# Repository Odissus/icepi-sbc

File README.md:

# Icepi SBC

A low-cost single-board computer for the H3 CPU: A cheap yet powerful Linux device that you can take anywhere.

| Interested? [Subscribe to updates!](https://cyao.dev/subscribe.html) | Check out [Icepi Zero](https://github.com/cheyao/icepi-zero) too |
| -------------------------------------------------------------------- | ---------------------------------------------------------------- |

If there's a lot of people interested, there's a chance that I'll try to sell this at a relatively low price :P

## Features

- H3 Quad-Core ARM Cortex-A7 @ 1.296GHz CPU
    - Mali400 MP2 OpenGL ES 2.0 GPU
- 512MiB of DDR3 RAM, stable at 696MHz (Upgradable to 1GiB)
- Ethernet PHY, WiFi & Bluetooth
- GPDI video out
- USB connectors:
    - 2x USB-A 
    - 2x USB-C (One OTG port)
    - 1x USB-C 100W PD power port
- 3.5mm audio jack
- uSD card slot
- eMMC 5.1 storage

## System support

The single-board computer is capable of running Linux (debian) and Android ([H3Droid](https://h3droid.com/project)). It can output 4k video via it's GPDI-A connector, output a tty consol via UART, or act as an remote host via ssh.

It's small, compact form factor allows it to be a nice portable computer that you can take anywhere! It supports GPU acceleration and 4k video decoding, letting you view anything in full confort.

## PCB

[Check out the online version here](https://github.com/cheyao/icepi-sbc/tree/main/hardware).

The PCB is only 4 layered, ensuring minimal cost and overhead during production. But for mass production 6 layers is recommended, putting solid ground on In.1 and In.4, then copy the power plane to In.2 and In.3. (Impedance matching might be required depending on stackup)

The current setup uses [JLCPCB's](https://jlcpcb.com/) JLC04161H-3313 stackup, and the BOM is optimized for use there. Using other fabs would require re-tuning the DDR3, USB and GPDI traces.

## Open source

This project is licensed under the [Solderpad](/LICENSE) hardware license, granting the maximum amount of liberty :)

It is also OSHWA certified under the identifier [FR000029](https://certification.oshwa.org/fr000029.html).

## Contact

Any questions? Dm `@Cyao.` on Discord (Send a friend request or join the KiCAD Discord server) or send an email to `cyao _at_ duck.com`!

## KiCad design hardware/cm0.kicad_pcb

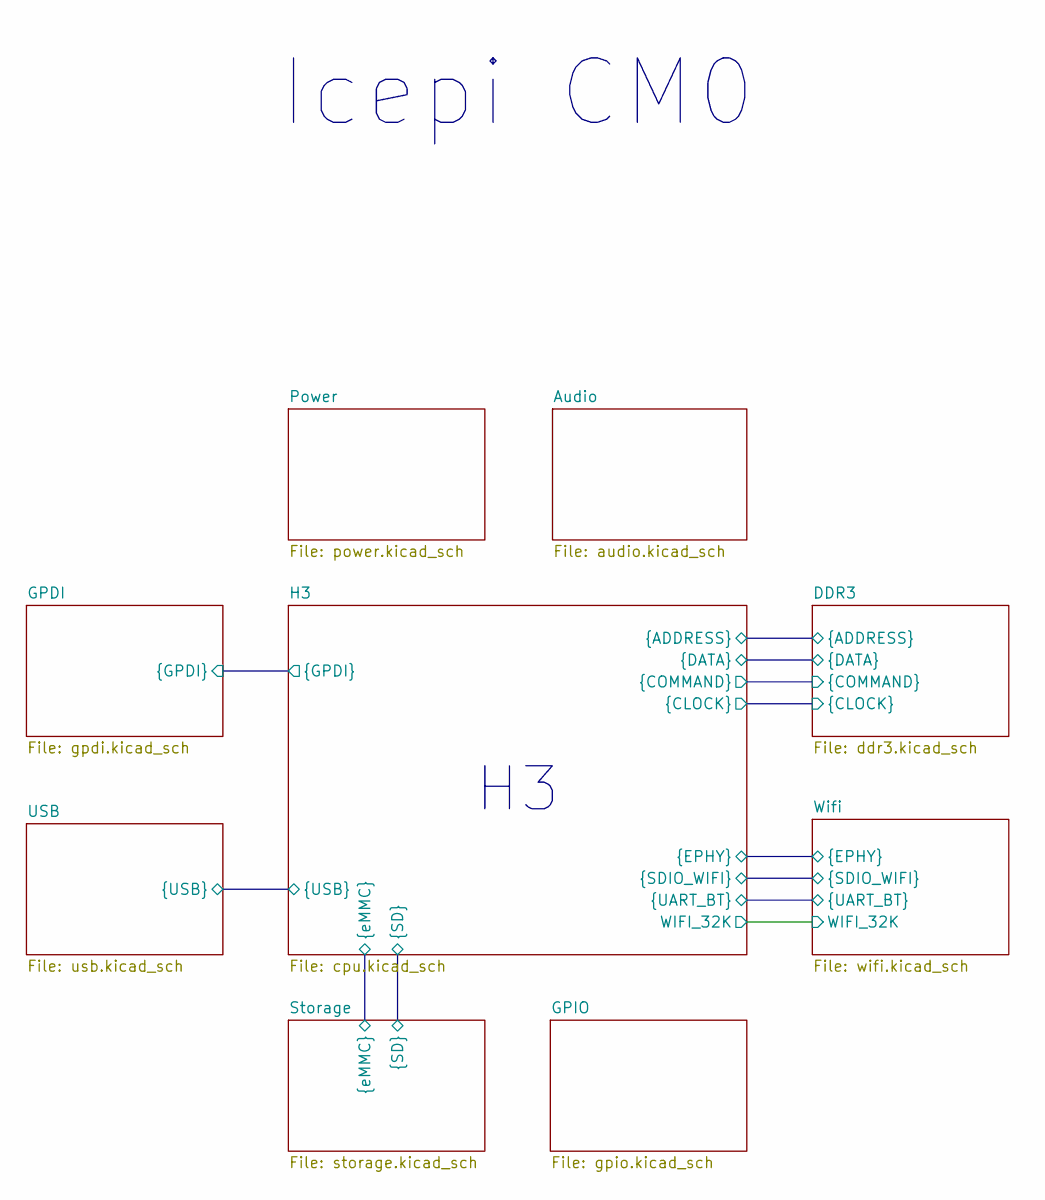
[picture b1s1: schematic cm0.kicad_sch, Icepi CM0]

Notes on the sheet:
Icepi CM0

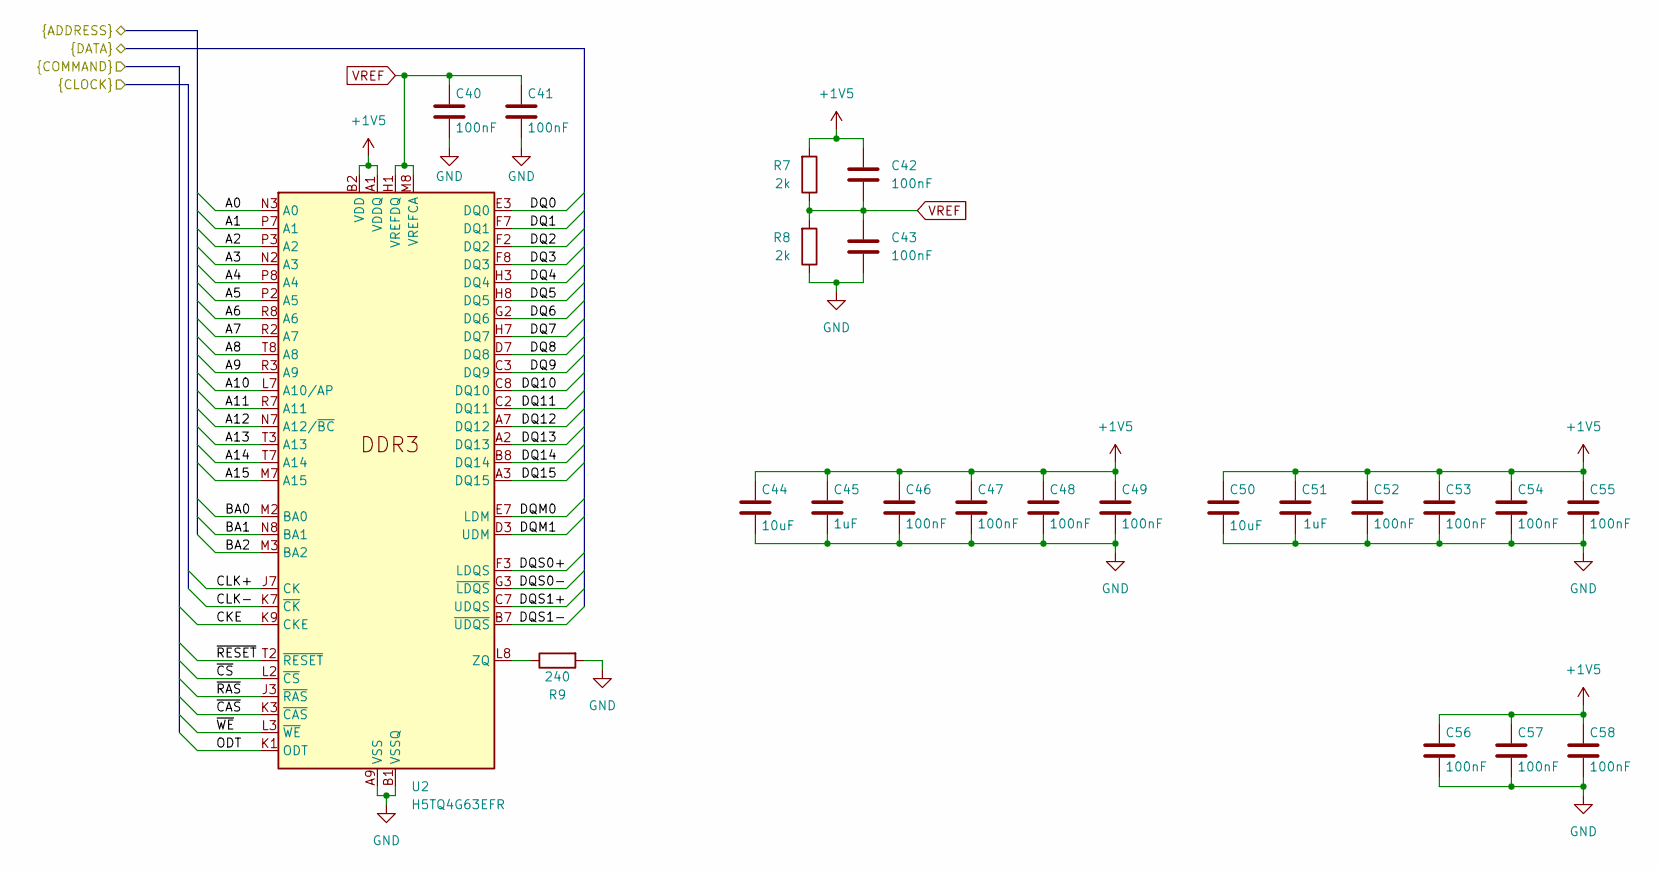
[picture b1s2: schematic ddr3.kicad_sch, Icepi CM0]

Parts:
C40, C41, C42, C43, C46, C47, C48, C49, C52, C53, C54, C55, C56, C57, C58: 100nF; C_0402_1005Metric; LCSC Part # C1525
C44, C50: 10uF; C_0603_1608Metric; LCSC Part # C19702
C45, C51: 1uF; C_0402_1005Metric; LCSC Part # C52923
R7, R8: 2k; R_0402_1005Metric; LCSC Part # C4109
R9: 240; R_0603_1608Metric; LCSC Part # C23350
U2: H5TQ4G63EFR; FBGA-96_7.5x13mm_Layout9x16_P0.8mm; LCSC Part # C2803259

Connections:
+1V5: C42.1, C44.1, C45.2, C46.1, C47.1, C48.1, C49.1, C50.1, C51.2, C52.1, C53.1, C54.1, C55.1, C56.1, C57.1, C58.1, R7.2, U2.A1 (VDDQ), U2.A8 (VDDQ), U2.B2 (VDD), U2.C1 (VDDQ), U2.C9 (VDDQ), U2.D2 (VDDQ), U2.D9 (VDD), U2.E9 (VDDQ), U2.F1 (VDDQ), U2.G7 (VDD), U2.H2 (VDDQ), U2.H9 (VDDQ), U2.K2 (VDD), U2.K8 (VDD), U2.N1 (VDD), U2.N9 (VDD), U2.R1 (VDD), U2.R9 (VDD); also elsewhere on the board
/DDR3/A0: U2.N3 (A0); also elsewhere on the board
/DDR3/A1: U2.P7 (A1); also elsewhere on the board
/DDR3/A2: U2.P3 (A2); also elsewhere on the board
/DDR3/A3: U2.N2 (A3); also elsewhere on the board
/DDR3/A4: U2.P8 (A4); also elsewhere on the board
/DDR3/A5: U2.P2 (A5); also elsewhere on the board
/DDR3/A6: U2.R8 (A6); also elsewhere on the board
/DDR3/A7: U2.R2 (A7); also elsewhere on the board
/DDR3/A8: U2.T8 (A8); also elsewhere on the board
/DDR3/A9: U2.R3 (A9); also elsewhere on the board
/DDR3/A10: U2.L7 (A10/AP); also elsewhere on the board
/DDR3/A11: U2.R7 (A11); also elsewhere on the board
/DDR3/A12: U2.N7 (A12/~BC); also elsewhere on the board
/DDR3/A13: U2.T3 (A13); also elsewhere on the board
/DDR3/A14: U2.T7 (A14); also elsewhere on the board
/DDR3/A15: U2.M7 (A15); also elsewhere on the board
/DDR3/BA0: U2.M2 (BA0); also elsewhere on the board
/DDR3/BA1: U2.N8 (BA1); also elsewhere on the board
/DDR3/BA2: U2.M3 (BA2); also elsewhere on the board
/DDR3/CKE: U2.K9 (CKE); also elsewhere on the board
/DDR3/CLK+: U2.J7 (CK); also elsewhere on the board
/DDR3/CLK-: U2.K7 (~CK); also elsewhere on the board
/DDR3/DQ0: U2.E3 (DQ0); also elsewhere on the board
/DDR3/DQ1: U2.F7 (DQ1); also elsewhere on the board
/DDR3/DQ2: U2.F2 (DQ2); also elsewhere on the board
/DDR3/DQ3: U2.F8 (DQ3); also elsewhere on the board
/DDR3/DQ4: U2.H3 (DQ4); also elsewhere on the board
/DDR3/DQ5: U2.H8 (DQ5); also elsewhere on the board
/DDR3/DQ6: U2.G2 (DQ6); also elsewhere on the board
/DDR3/DQ7: U2.H7 (DQ7); also elsewhere on the board
/DDR3/DQ8: U2.D7 (DQ8); also elsewhere on the board
/DDR3/DQ9: U2.C3 (DQ9); also elsewhere on the board
/DDR3/DQ10: U2.C8 (DQ10); also elsewhere on the board
/DDR3/DQ11: U2.C2 (DQ11); also elsewhere on the board
/DDR3/DQ12: U2.A7 (DQ12); also elsewhere on the board
/DDR3/DQ13: U2.A2 (DQ13); also elsewhere on the board
/DDR3/DQ14: U2.B8 (DQ14); also elsewhere on the board
/DDR3/DQ15: U2.A3 (DQ15); also elsewhere on the board
/DDR3/DQM0: U2.E7 (LDM); also elsewhere on the board
/DDR3/DQM1: U2.D3 (UDM); also elsewhere on the board
/DDR3/DQS0+: U2.F3 (LDQS); also elsewhere on the board
/DDR3/DQS0-: U2.G3 (~LDQS); also elsewhere on the board
/DDR3/DQS1+: U2.C7 (UDQS); also elsewhere on the board
/DDR3/DQS1-: U2.B7 (~UDQS); also elsewhere on the board
/DDR3/ODT: U2.K1 (ODT); also elsewhere on the board
/DDR3/~CAS: U2.K3 (~CAS); also elsewhere on the board
/DDR3/~CS: U2.L2 (~CS); also elsewhere on the board
/DDR3/~RAS: U2.J3 (~RAS); also elsewhere on the board
/DDR3/~RESET: U2.T2 (~RESET); also elsewhere on the board
/DDR3/~WE: U2.L3 (~WE); also elsewhere on the board
GND: C40.2, C41.2, C43.2, C44.2, C45.1, C46.2, C47.2, C48.2, C49.2, C50.2, C51.1, C52.2, C53.2, C54.2, C55.2, C56.2, C57.2, C58.2, R8.1, R9.2, U2.A9 (VSS), U2.B1 (VSSQ), U2.B3 (VSS), U2.B9 (VSSQ), U2.D1 (VSSQ), U2.D8 (VSSQ), U2.E1 (VSS), U2.E2 (VSSQ), U2.E8 (VSSQ), U2.F9 (VSSQ), U2.G1 (VSSQ), U2.G8 (VSS), U2.G9 (VSSQ), U2.J2 (VSS), U2.J8 (VSS), U2.M1 (VSS), U2.M9 (VSS), U2.P1 (VSS), U2.P9 (VSS), U2.T1 (VSS), U2.T9 (VSS); also elsewhere on the board
unnamed: R9.1, U2.L8 (ZQ)
VREF: C40.1, C41.1, C42.2, C43.1, R7.1, R8.2, U2.H1 (VREFDQ), U2.M8 (VREFCA); also elsewhere on the board

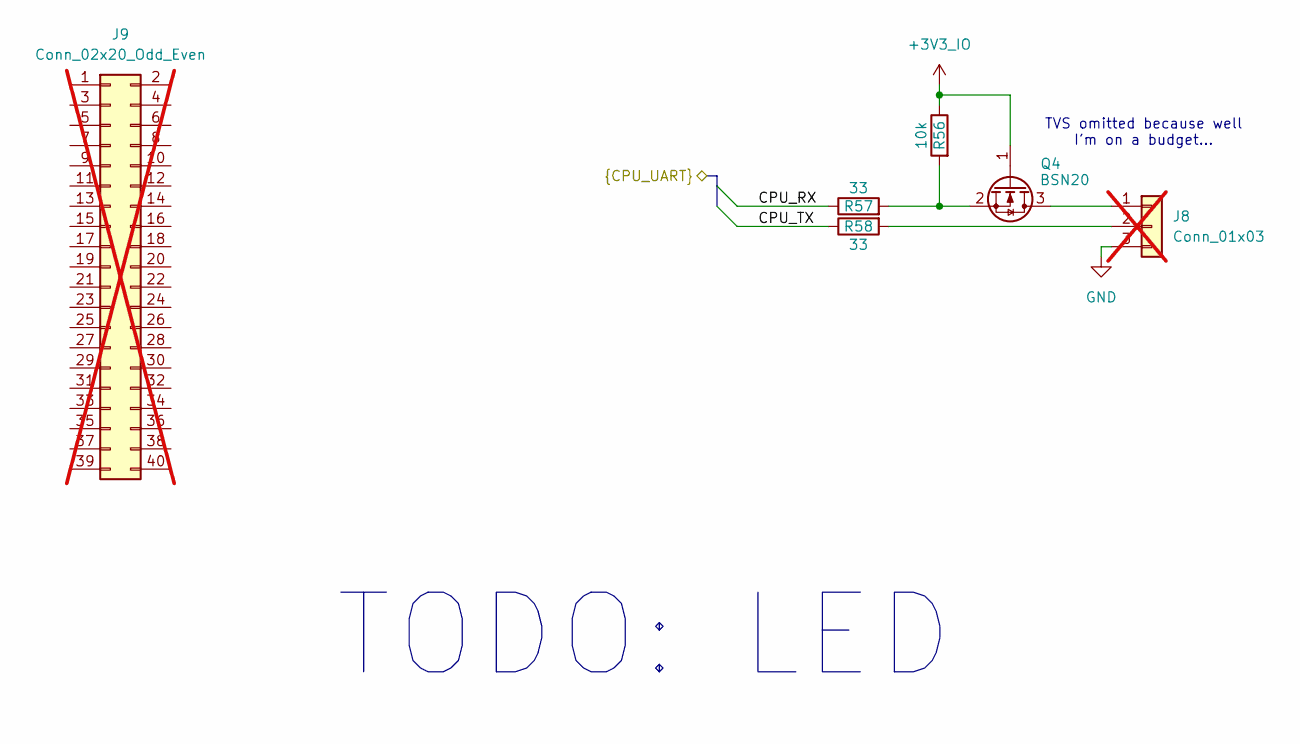
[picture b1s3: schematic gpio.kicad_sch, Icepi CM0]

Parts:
J8: Conn_01x03; PinHeader_1x03_P2.54mm_Vertical; not fitted
J9: Conn_02x20_Odd_Even; PinHeader_2x20_P2.54mm_Vertical; not fitted
Q4: BSN20; SOT-23; LCSC Part # C116157
R56: 10k; R_0402_1005Metric; LCSC Part # C25744
R57, R58: 33; R_0402_1005Metric; LCSC Part # C25105

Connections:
+3V3_IO: Q4.1 (G), R56.1; also elsewhere on the board
/GPIO/CPU_RX: R57.1; also elsewhere on the board
/GPIO/CPU_TX: R58.1; also elsewhere on the board
GND: J8.3; also elsewhere on the board
unnamed: J8.1, Q4.3 (D)
unnamed: J8.2, R58.2
unnamed: Q4.2 (S), R56.2, R57.2

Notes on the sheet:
TODO: LED
TVS omitted because well I'm on a budget...

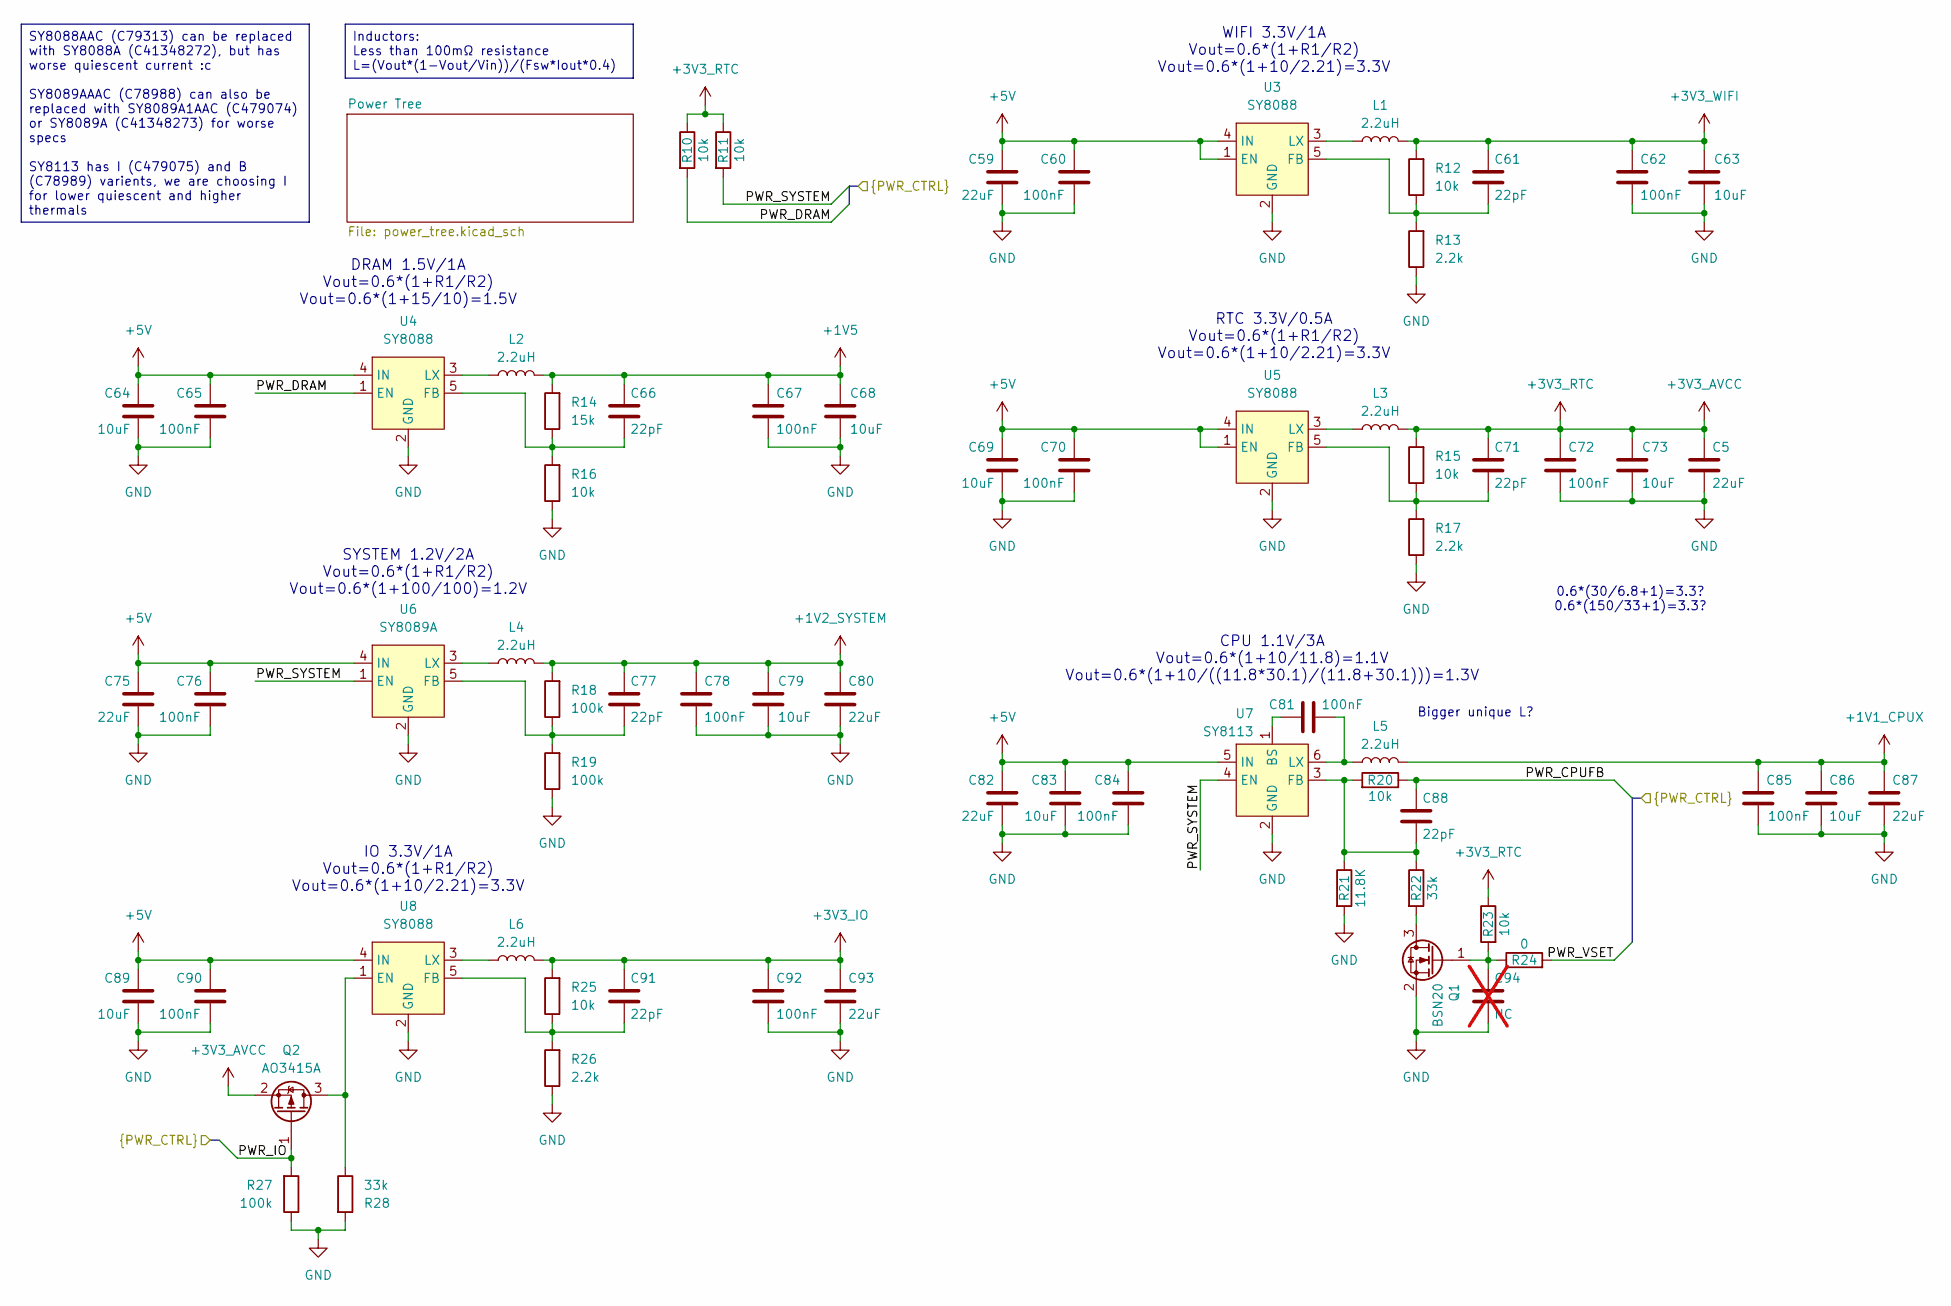
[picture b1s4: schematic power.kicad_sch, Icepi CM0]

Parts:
C5, C59, C75, C80, C82, C87, C93: 22uF; C_0603_1608Metric; LCSC Part # C59461
C60, C62, C65, C67, C70, C72, C76, C78, C81, C84, C85, C90, C92: 100nF; C_0402_1005Metric; LCSC Part # C1525
C61, C66, C71, C77, C88, C91: 22pF; C_0402_1005Metric; LCSC Part # C1555
C63, C64, C68, C69, C73, C79, C83, C86, C89: 10uF; C_0603_1608Metric; LCSC Part # C19702
C94: NC; C_0402_1005Metric; not fitted
L1, L2, L3, L6: 2.2uH; L_Sunlord_SWPA3015S; LCSC Part # C19734
L4, L5: 2.2uH; L_Sunlord_SWPA4030S; LCSC Part # C135262
Q1: BSN20; SOT-23; LCSC Part # C116157
Q2: AO3415A; SOT-23; LCSC Part # C347479
R10, R11, R12, R15, R16, R20, R23, R25: 10k; R_0402_1005Metric; LCSC Part # C25744
R13, R17, R26: 2.2k; R_0402_1005Metric; LCSC Part # C25879
R14: 15k; R_0402_1005Metric; LCSC Part # C25756
R18, R19, R27: 100k; R_0402_1005Metric; LCSC Part # C25741
R21: 11.8K; R_0402_1005Metric; LCSC Part # C2929934
R22, R28: 33k; R_0402_1005Metric; LCSC Part # C25779
R24: 0; R_0402_1005Metric; LCSC Part # C17168
U3, U4, U5, U8: SY8088; SOT-23-5; LCSC Part # C79313
U6: SY8089A; SOT-23-5; LCSC Part # C78988
U7: SY8113; TSOT-23-6; LCSC Part # C479075

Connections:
+1V1_CPUX: C85.2, C86.1, C87.1, L5.2; also elsewhere on the board
+1V2_SYSTEM: C77.1, C78.2, C79.1, C80.1, L4.2, R18.2; also elsewhere on the board
+1V5: C66.1, C67.2, C68.1, L2.2, R14.2; also elsewhere on the board
+3V3_AVCC: C5.1, C71.1, C72.2, C73.1, L3.2, Q2.2 (S), R10.1, R11.1, R15.2, R23.1; also elsewhere on the board
+3V3_IO: C91.1, C92.2, C93.1, L6.2, R25.2; also elsewhere on the board
+3V3_WIFI: C61.1, C62.2, C63.1, L1.2, R12.2; also elsewhere on the board
+5V: C59.1, C60.2, C64.1, C65.2, C69.1, C70.2, C75.1, C76.2, C82.1, C83.1, C84.2, C89.1, C90.2, U3.1 (EN), U3.4 (IN), U4.4 (IN), U5.1 (EN), U5.4 (IN), U6.4 (IN), U7.5 (IN), U8.4 (IN); also elsewhere on the board
/H3/PWR_CPUFB: C88.1, R20.1; also elsewhere on the board
/H3/PWR_DRAM: R10.2, U4.1 (EN); also elsewhere on the board
/H3/PWR_IO: Q2.1 (G), R27.2; also elsewhere on the board
/H3/PWR_SYSTEM: R11.2, U6.1 (EN), U7.4 (EN); also elsewhere on the board
/H3/PWR_VSET: R24.2; also elsewhere on the board
GND: C5.2, C59.2, C60.1, C62.1, C63.2, C64.2, C65.1, C67.1, C68.2, C69.2, C70.1, C72.1, C73.2, C75.2, C76.1, C78.1, C79.2, C80.2, C82.2, C83.2, C84.1, C85.1, C86.2, C87.2, C89.2, C90.1, C92.1, C93.2, C94.2, Q1.2 (S), R13.1, R16.1, R17.1, R19.1, R21.2, R26.1, R27.1, R28.2, U3.2 (GND), U4.2 (GND), U5.2 (GND), U6.2 (GND), U7.2 (GND), U8.2 (GND); also elsewhere on the board
unnamed: Q1.3 (D), R22.2
unnamed: C94.1, Q1.1 (G), R23.2, R24.1
unnamed: Q2.3 (D), R28.1, U8.1 (EN)
unnamed: C61.2, R12.1, R13.2, U3.5 (FB)
unnamed: L1.1, U3.3 (LX)
unnamed: C66.2, R14.1, R16.2, U4.5 (FB)
unnamed: L2.1, U4.3 (LX)
unnamed: C71.2, R15.1, R17.2, U5.5 (FB)
unnamed: L3.1, U5.3 (LX)
unnamed: C77.2, R18.1, R19.2, U6.5 (FB)
unnamed: L4.1, U6.3 (LX)
unnamed: C81.2, U7.1 (BS)
unnamed: C88.2, R20.2, R21.1, R22.1, U7.3 (FB)
unnamed: C81.1, L5.1, U7.6 (LX)
unnamed: C91.2, R25.1, R26.2, U8.5 (FB)
unnamed: L6.1, U8.3 (LX)

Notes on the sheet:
SYSTEM 1.2V/2A Vout=0.6*(1+R1/R2) Vout=0.6*(1+100/100)=1.2V
WIFI 3.3V/1A Vout=0.6*(1+R1/R2) Vout=0.6*(1+10/2.21)=3.3V
0.6*(30/6.8+1)=3.3? 0.6*(150/33+1)=3.3?
RTC 3.3V/0.5A Vout=0.6*(1+R1/R2) Vout=0.6*(1+10/2.21)=3.3V
IO 3.3V/1A Vout=0.6*(1+R1/R2) Vout=0.6*(1+10/2.21)=3.3V
CPU 1.1V/3A Vout=0.6*(1+10/11.8)=1.1V Vout=0.6*(1+10/((11.8*30.1)/(11.8+30.1)))=1.3V
DRAM 1.5V/1A Vout=0.6*(1+R1/R2) Vout=0.6*(1+15/10)=1.5V
Bigger unique L?
SY8088AAC (C79313) can be replaced with SY8088A (C41348272), but has worse quiescent current :c SY8089AAAC (C78988) can also be replaced with SY8089A1AAC (C479074) or SY8089A (C41348273) for worse specs SY8113 has I (C479075) and B (C78989) varients, we are choosing I for lower quiescent and higher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
Inductors: Less than 100mΩ resistance L=(Vout*(1-Vout/Vin))/(Fsw*Iout*0.4)

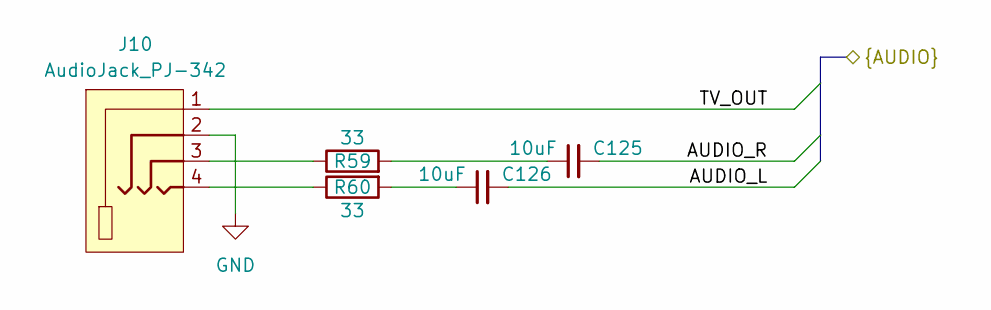
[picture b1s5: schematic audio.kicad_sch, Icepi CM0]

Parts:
C125, C126: 10uF; C_0603_1608Metric; LCSC Part # C19702
J10: AudioJack_PJ-342; Jack_3.5mm_SHOUHAN_PJ-342; LCSC Part # C7507452
R59, R60: 33; R_0402_1005Metric; LCSC Part # C25105

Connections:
/Audio/AUDIO_L: C126.2; also elsewhere on the board
/Audio/AUDIO_R: C125.2; also elsewhere on the board
/Audio/TV_OUT: J10.1; also elsewhere on the board
GND: J10.2; also elsewhere on the board
unnamed: C125.1, R59.2
unnamed: C126.1, R60.2
unnamed: J10.3, J10.5, R59.1
unnamed: J10.4, J10.6, R60.1

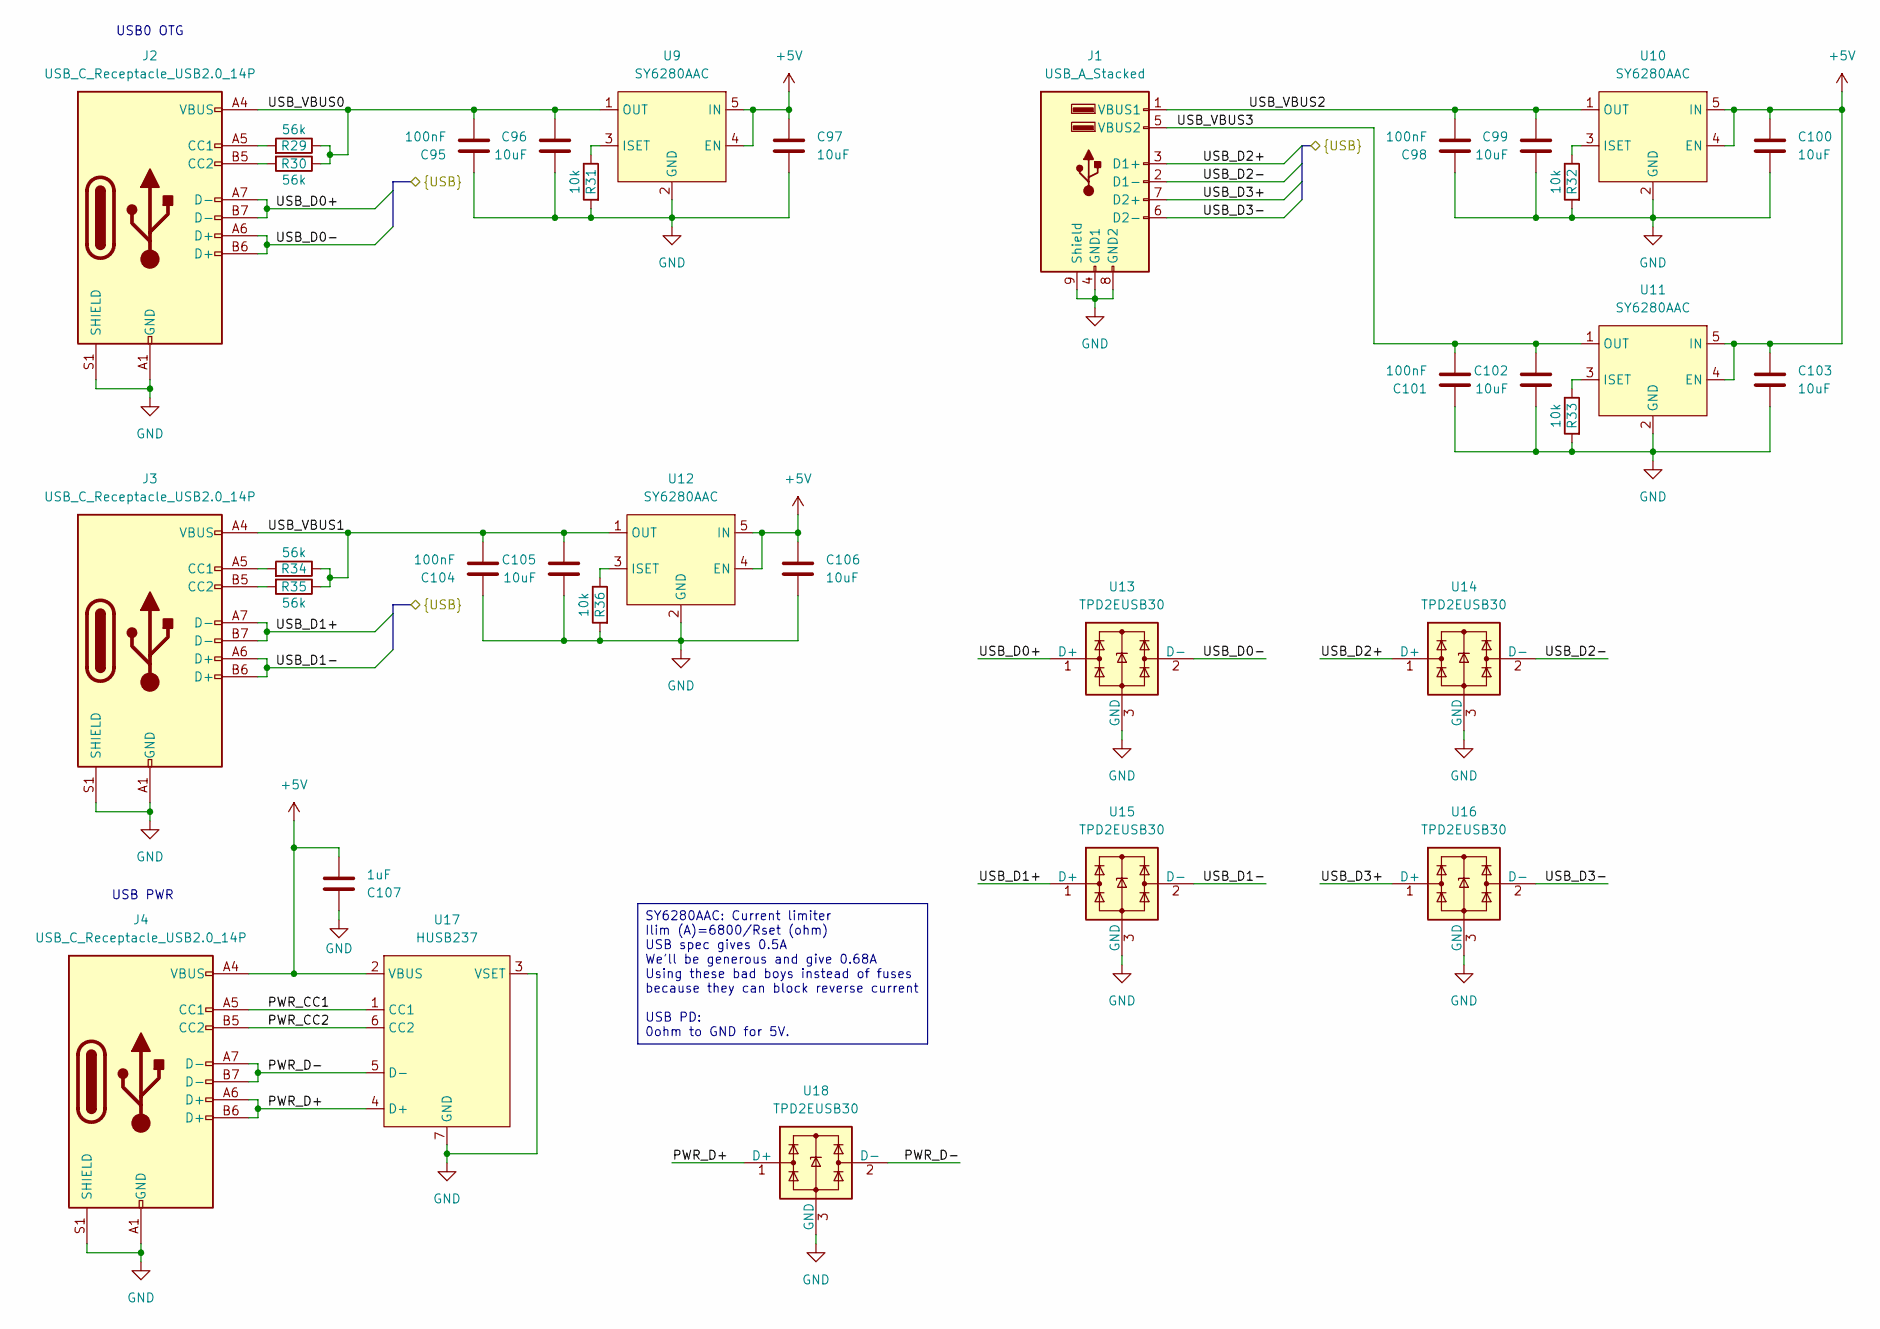
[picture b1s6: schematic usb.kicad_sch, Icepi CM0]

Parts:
C95, C98, C101, C104: 100nF; C_0402_1005Metric; LCSC Part # C1525
C96, C97, C99, C100, C102, C103, C105, C106: 10uF; C_0603_1608Metric; LCSC Part # C19702
C107: 1uF; C_0402_1005Metric; LCSC Part # C52923
J1: USB_A_Stacked; USB_A_SHOUHAN_AF_SS-JB17.6_Horizontal_Stacked; LCSC Part # C456021
J2, J3, J4: USB_C_Receptacle_USB2.0_14P; USB_C_Receptacle_HRO_TYPE-C-31-M-12; LCSC Part # C165948
R29, R30, R34, R35: 56k; R_0402_1005Metric; LCSC Part # C25796
R31, R32, R33, R36: 10k; R_0402_1005Metric; LCSC Part # C25744
U9, U10, U11, U12: SY6280AAC; SOT-23-5; LCSC Part # C55136
U13, U14, U15, U16, U18: TPD2EUSB30; Texas_DRT-3; LCSC Part # C5182099
U17: HUSB237; DFN-6-1EP_2x2mm_P0.65mm_EP1x1.6mm; LCSC Part # C22373734

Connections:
+5V: C97.1, C100.1, C103.1, C106.1, C107.2, J4.A4 (VBUS), J4.A9 (VBUS), J4.B4 (VBUS), J4.B9 (VBUS), U9.4 (EN), U9.5 (IN), U10.4 (EN), U10.5 (IN), U11.4 (EN), U11.5 (IN), U12.4 (EN), U12.5 (IN), U17.2 (VBUS); also elsewhere on the board
/H3/USB_D0+: J2.A7 (D-), J2.B7 (D-), U13.1 (D+); also elsewhere on the board
/H3/USB_D0-: J2.A6 (D+), J2.B6 (D+), U13.2 (D-); also elsewhere on the board
/H3/USB_D1+: J3.A7 (D-), J3.B7 (D-), U15.1 (D+); also elsewhere on the board
/H3/USB_D1-: J3.A6 (D+), J3.B6 (D+), U15.2 (D-); also elsewhere on the board
/USB/PWR_CC1: J4.A5 (CC1), U17.1 (CC1)
/USB/PWR_CC2: J4.B5 (CC2), U17.6 (CC2)
/USB/PWR_D+: J4.A6 (D+), J4.B6 (D+), U17.4 (D+), U18.1 (D+)
/USB/PWR_D-: J4.A7 (D-), J4.B7 (D-), U17.5 (D-), U18.2 (D-)
/USB/USB_VBUS0: C95.2, C96.1, J2.A4 (VBUS), J2.A9 (VBUS), J2.B4 (VBUS), J2.B9 (VBUS), R29.1, R30.1, U9.1 (OUT)
/USB/USB_VBUS1: C104.2, C105.1, J3.A4 (VBUS), J3.A9 (VBUS), J3.B4 (VBUS), J3.B9 (VBUS), R34.1, R35.1, U12.1 (OUT)
/USB/USB_VBUS2: C98.2, C99.1, J1.1 (VBUS1), U10.1 (OUT)
/USB/USB_VBUS3: C101.2, C102.1, J1.5 (VBUS2), U11.1 (OUT)
GND: C95.1, C96.2, C97.2, C98.1, C99.2, C100.2, C101.1, C102.2, C103.2, C104.1, C105.2, C106.2, C107.1, J1.4 (GND1), J1.8 (GND2), J1.9 (Shield), J2.A1 (GND), J2.A12 (GND), J2.B1 (GND), J2.B12 (GND), J2.S1 (SHIELD), J3.A1 (GND), J3.A12 (GND), J3.B1 (GND), J3.B12 (GND), J3.S1 (SHIELD), J4.A1 (GND), J4.A12 (GND), J4.B1 (GND), J4.B12 (GND), J4.S1 (SHIELD), R31.2, R32.2, R33.2, R36.2, U9.2 (GND), U10.2 (GND), U11.2 (GND), U12.2 (GND), U13.3 (GND), U14.3 (GND), U15.3 (GND), U16.3 (GND), U17.3 (VSET), U17.7 (GND), U18.3 (GND); also elsewhere on the board
unnamed: J2.A5 (CC1), R29.2
unnamed: J2.B5 (CC2), R30.2
unnamed: J3.A5 (CC1), R34.2
unnamed: J3.B5 (CC2), R35.2
unnamed: R31.1, U9.3 (ISET)
unnamed: R32.1, U10.3 (ISET)
unnamed: R33.1, U11.3 (ISET)
unnamed: R36.1, U12.3 (ISET)

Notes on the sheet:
USB0 OTG
USB PWR
SY6280AAC: Current limiter Ilim (A)=6800/Rset (ohm) USB spec gives 0.5A We'll be generous and give 0.68A Using these bad boys instead of fuses because they can block reverse current USB PD: 0ohm to GND for 5V.

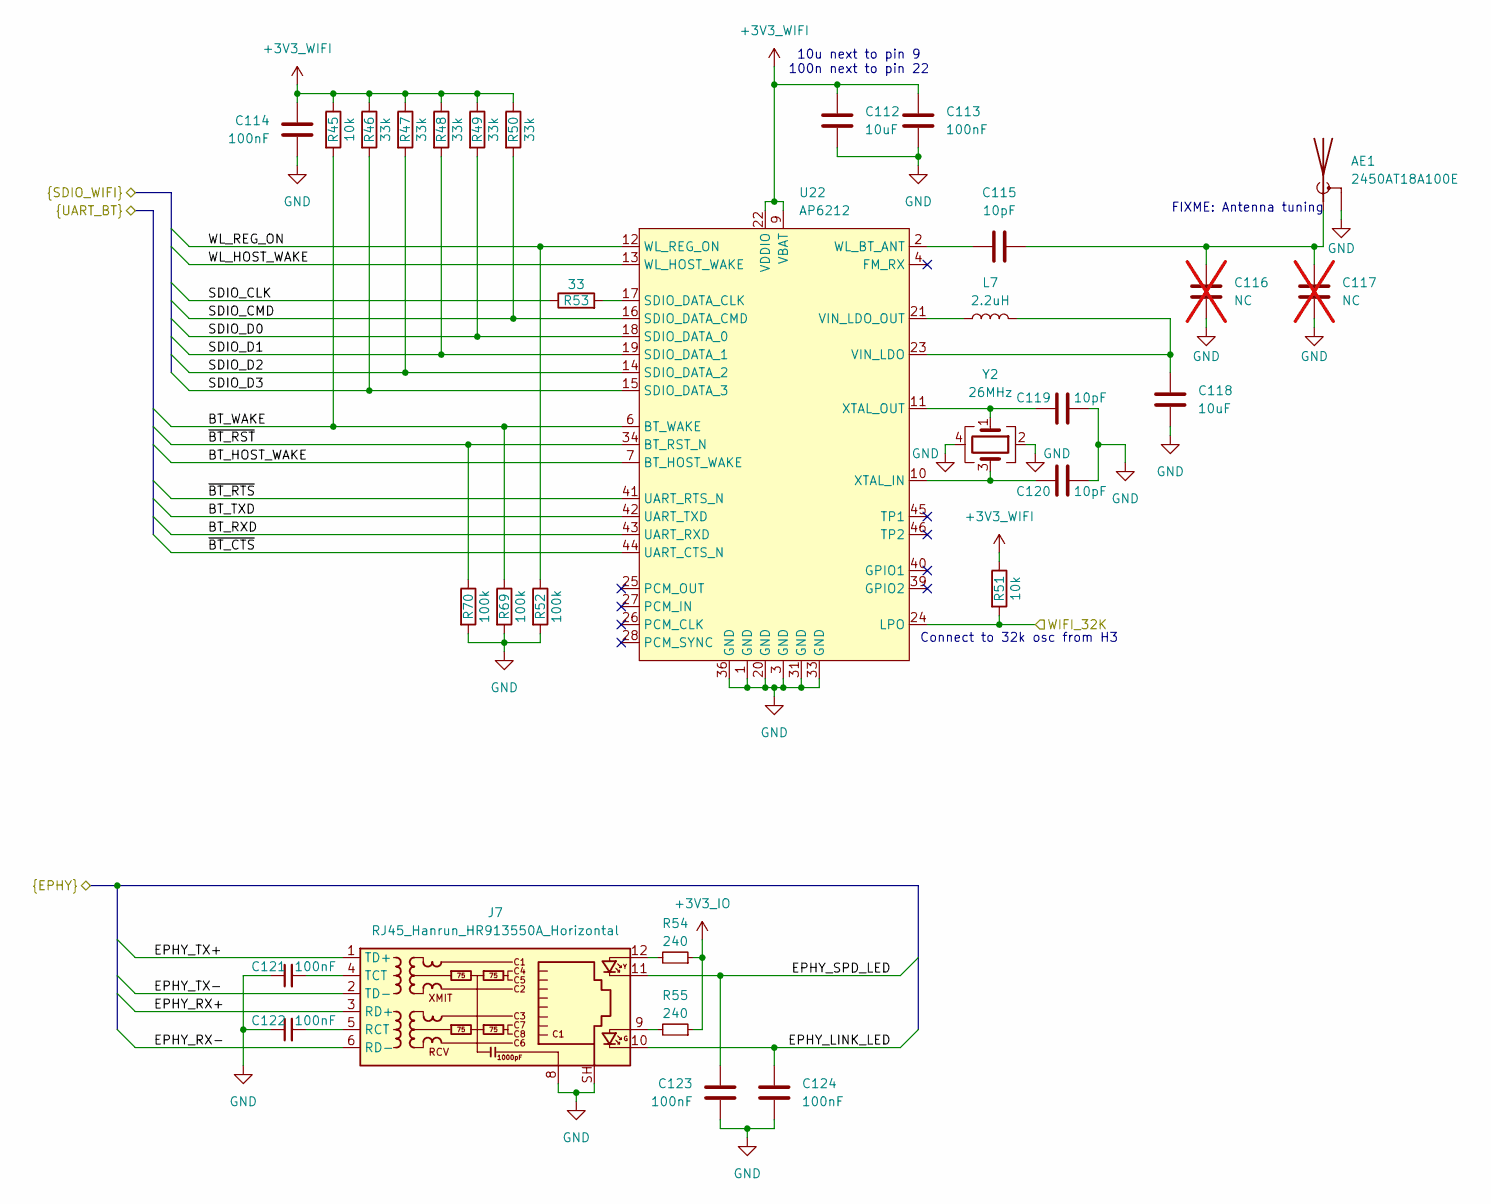
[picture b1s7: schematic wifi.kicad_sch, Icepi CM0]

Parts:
AE1: 2450AT18A100E; Johanson_2450AT18x100; LCSC Part # C89334
C112, C118: 10uF; C_0603_1608Metric; LCSC Part # C19702
C113, C114, C121, C122, C123, C124: 100nF; C_0402_1005Metric; LCSC Part # C1525
C115, C119, C120: 10pF; C_0402_1005Metric; LCSC Part # C32949
C116, C117: NC; C_0402_1005Metric; not fitted
J7: RJ45_Hanrun_HR913550A_Horizontal; RJ45_Hanrun_HR911105A_Horizontal; LCSC Part # C163507
L7: 2.2uH; L_Sunlord_SWPA3015S; LCSC Part # C19734
R45, R51: 10k; R_0402_1005Metric; LCSC Part # C25744
R46, R47, R48, R49, R50: 33k; R_0402_1005Metric; LCSC Part # C25779
R52, R69, R70: 100k; R_0402_1005Metric; LCSC Part # C25741
R53: 33; R_0402_1005Metric; LCSC Part # C25105
R54, R55: 240; R_0603_1608Metric; LCSC Part # C23350
U22: AP6212; LCSC Part # C2798300
Y2: 26MHz; Crystal_SMD_2016-4Pin_2.0x1.6mm; LCSC Part # C7294683

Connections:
+3V3_IO: R54.1, R55.1; also elsewhere on the board
+3V3_WIFI: C112.1, C113.1, C114.1, R45.1, R46.1, R47.1, R48.1, R49.1, R50.1, R51.1, U22.9 (VBAT), U22.22 (VDDIO); also elsewhere on the board
/H3/BT_HOST_WAKE: U22.7 (BT_HOST_WAKE); also elsewhere on the board
/H3/BT_RXD: U22.43 (UART_RXD); also elsewhere on the board
/H3/BT_TXD: U22.42 (UART_TXD); also elsewhere on the board
/H3/BT_WAKE: R45.2, R69.1, U22.6 (BT_WAKE); also elsewhere on the board
/H3/EPHY_LINK_LED: C124.1, J7.10; also elsewhere on the board
/H3/EPHY_RX+: J7.3 (RD+); also elsewhere on the board
/H3/EPHY_RX-: J7.6 (RD-); also elsewhere on the board
/H3/EPHY_SPD_LED: C123.1, J7.11; also elsewhere on the board
/H3/EPHY_TX+: J7.1 (TD+); also elsewhere on the board
/H3/EPHY_TX-: J7.2 (TD-); also elsewhere on the board
/H3/SDIO_CLK: R53.1; also elsewhere on the board
/H3/SDIO_CMD: R50.2, U22.16 (SDIO_DATA_CMD); also elsewhere on the board
/H3/SDIO_D0: R49.2, U22.18 (SDIO_DATA_0); also elsewhere on the board
/H3/SDIO_D1: R48.2, U22.19 (SDIO_DATA_1); also elsewhere on the board
/H3/SDIO_D2: R47.2, U22.14 (SDIO_DATA_2); also elsewhere on the board
/H3/SDIO_D3: R46.2, U22.15 (SDIO_DATA_3); also elsewhere on the board
/H3/WIFI_32K: R51.2, U22.24 (LPO); also elsewhere on the board
/H3/WL_HOST_WAKE: U22.13 (WL_HOST_WAKE); also elsewhere on the board
/H3/WL_REG_ON: R52.1, U22.12 (WL_REG_ON); also elsewhere on the board
/H3/~BT_CTS: U22.44 (UART_CTS_N); also elsewhere on the board
/H3/~BT_RST: R70.1, U22.34 (BT_RST_N); also elsewhere on the board
/H3/~BT_RTS: U22.41 (UART_RTS_N); also elsewhere on the board
GND: AE1.2 (Shield), C112.2, C113.2, C114.2, C116.2, C117.2, C118.2, C119.2, C120.2, C121.1, C122.1, C123.2, C124.2, J7.8, J7.SH, R52.2, R69.2, R70.2, U22.1 (GND), U22.3 (GND), U22.20 (GND), U22.31 (GND), U22.33 (GND), U22.36 (GND), Y2.2, Y2.4; also elsewhere on the board
unnamed: AE1.1 (A), C115.2, C116.1, C117.1
unnamed: J7.9, R55.2
unnamed: J7.12, R54.2
unnamed: C122.2, J7.5 (RCT)
unnamed: C121.2, J7.4 (TCT)
unnamed: R53.2, U22.17 (SDIO_DATA_CLK)
unnamed: C118.1, L7.2, U22.23 (VIN_LDO)
unnamed: L7.1, U22.21 (VIN_LDO_OUT)
unnamed: C115.1, U22.2 (WL_BT_ANT)
unnamed: C120.1, U22.10 (XTAL_IN), Y2.3
unnamed: C119.1, U22.11 (XTAL_OUT), Y2.1

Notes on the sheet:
FIXME: Antenna tuning
10u next to pin 9 100n next to pin 22
Connect to 32k osc from H3

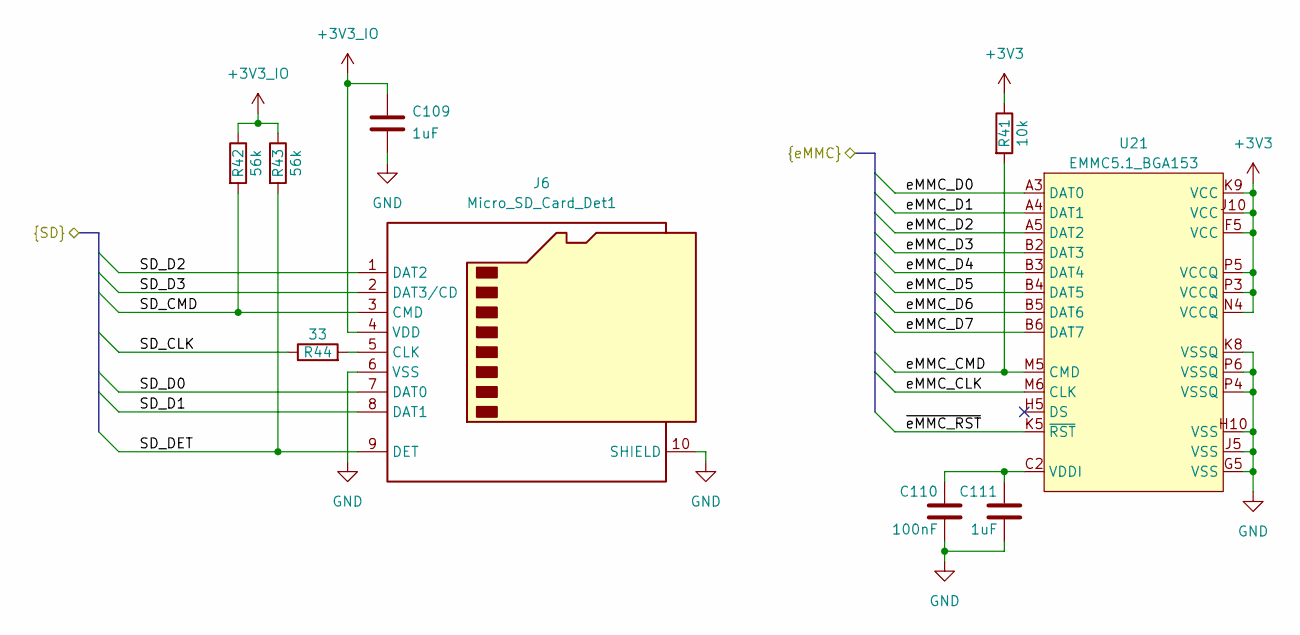
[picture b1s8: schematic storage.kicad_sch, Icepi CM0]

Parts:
C109, C111: 1uF; C_0402_1005Metric; LCSC Part # C52923
C110: 100nF; C_0402_1005Metric; LCSC Part # C1525
J6: Micro_SD_Card_Det1; microSD_TF-01A; LCSC Part # C2889258
R41: 10k; R_0402_1005Metric; LCSC Part # C25744
R42, R43: 56k; R_0402_1005Metric; LCSC Part # C25796
R44: 33; R_0402_1005Metric; LCSC Part # C25105
U21: EMMC5.1_BGA153; LFBGA-153_11.5x13mm_Layout14x14_P0.5mm

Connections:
+3V3: R41.1, U21.C6 (VCCQ), U21.E6 (VCC), U21.F5 (VCC), U21.J10 (VCC), U21.K9 (VCC), U21.M4 (VCCQ), U21.N4 (VCCQ), U21.P3 (VCCQ), U21.P5 (VCCQ); also elsewhere on the board
+3V3_IO: C109.2, J6.4 (VDD), R42.1, R43.1; also elsewhere on the board
/H3/SD_CLK: R44.1; also elsewhere on the board
/H3/SD_CMD: J6.3 (CMD), R42.2; also elsewhere on the board
/H3/SD_D0: J6.7 (DAT0); also elsewhere on the board
/H3/SD_D1: J6.8 (DAT1); also elsewhere on the board
/H3/SD_D2: J6.1 (DAT2); also elsewhere on the board
/H3/SD_D3: J6.2 (DAT3/CD); also elsewhere on the board
/H3/SD_DET: J6.9 (DET), R43.2; also elsewhere on the board
/H3/eMMC_CLK: U21.M6 (CLK); also elsewhere on the board
/H3/eMMC_CMD: R41.2, U21.M5 (CMD); also elsewhere on the board
/H3/eMMC_D0: U21.A3 (DAT0); also elsewhere on the board
/H3/eMMC_D1: U21.A4 (DAT1); also elsewhere on the board
/H3/eMMC_D2: U21.A5 (DAT2); also elsewhere on the board
/H3/eMMC_D3: U21.B2 (DAT3); also elsewhere on the board
/H3/eMMC_D4: U21.B3 (DAT4); also elsewhere on the board
/H3/eMMC_D5: U21.B4 (DAT5); also elsewhere on the board
/H3/eMMC_D6: U21.B5 (DAT6); also elsewhere on the board
/H3/eMMC_D7: U21.B6 (DAT7); also elsewhere on the board
/H3/~eMMC_RST: U21.K5 (~RST); also elsewhere on the board
GND: C109.1, C110.2, C111.1, J6.6 (VSS), J6.10 (SHIELD), U21.A6 (VSS), U21.C4 (VSSQ), U21.E7 (VSS), U21.G5 (VSS), U21.H10 (VSS), U21.J5 (VSS), U21.K8 (VSSQ), U21.N2 (VSSQ), U21.N5 (VSSQ), U21.P4 (VSSQ), U21.P6 (VSSQ); also elsewhere on the board
unnamed: J6.5 (CLK), R44.2
unnamed: C110.1, C111.2, U21.C2 (VDDI)
